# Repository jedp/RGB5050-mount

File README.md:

# RGB5050-mount

Revision 1.

A board for mounting [RGB 5050
LED](https://www.digikey.com/en/products/detail/inolux/IN-PI554FCH/7604874)s.

Note that the four things that are rendered as rings in the four corners are
actually cut as castellations on the board, so you can solder it down to power
rails like copper tape.

## Why

I am working on a [project](https://github.com/jed/window-tetris) that requires
a large number of RGB LEDs spread out at a social distance of about 3 inches
from each other. This board lets me do that easily.

## Prototyping

This design is also breadboard-friendly. The two rows of connections are 0.6
inches apart, so if you solder some headers into them, they will sit nicely on
a breadboard.

## Gerber Files

The gerber files are already exported in `export/gerber/` if you just want to
take them and go.

## BOM

- [5050
  LED](https://www.digikey.com/en/products/detail/inolux/IN-PI554FCH/7604874)
- 0.1μF 0803 ceramic capacitor

## License

Written by Jed Parsons. Distributed under the BSD license. Read `license.txt`
for details. All text above must be included in any redistribution.

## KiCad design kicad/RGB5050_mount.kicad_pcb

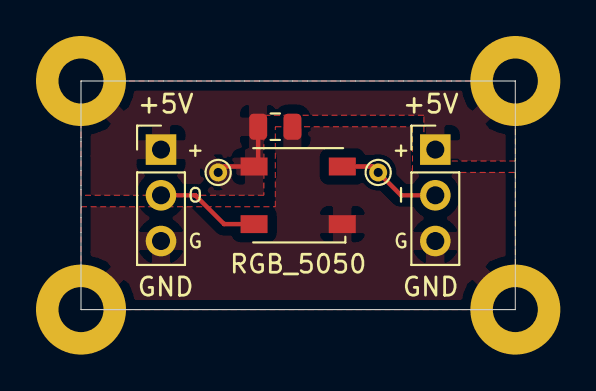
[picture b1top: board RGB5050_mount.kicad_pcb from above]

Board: 2 copper layers, 24.1 x 12.7 mm, 12 parts (0 on the bottom side), 4 nets.

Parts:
C1: C_Small; C_0805_2012Metric
H1_Large1, H2_Large1, H3_Large1, H4_Large1: MountingHole_Pad; MountingHole_2.5mm_Pad
J1, J2: Conn_01x03_Female; PinHeader_1x03_P2.54mm_Vertical
RGB_5050: Inolux_IN-PI554FCH; LED_Inolux_IN-PI554FCH_PLCC4_5.0x5.0mm_P3.2mm
TP1, TP2: TestPoint; TestPoint_THTPad_D1.0mm_Drill0.5mm
svg2mod, svg2mod#2: G***; drainmouse

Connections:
+5V: C1.1, H2_Large1.1, H3_Large1.1, J1.1, J2.1, RGB_5050.3, TP1.1
D_IN: J1.2, RGB_5050.2, TP2.1
D_OUT: J2.2, RGB_5050.4
GND: C1.2, H1_Large1.1, H4_Large1.1, J1.3, J2.3, RGB_5050.1

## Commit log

2020-10-08 PCB for mounting an RBG5050 LED
